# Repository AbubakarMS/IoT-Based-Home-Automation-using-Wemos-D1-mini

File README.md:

# IoT-Based-Home-Automation-using-Wemos-D1-mini
This project utilizes the D1 Mini and Blynk IoT platforms to monitor and control appliances. Users can switch appliances on and off through a mobile phone, providing a convenient and efficient home automation solution.

Note: A Kicad project files.

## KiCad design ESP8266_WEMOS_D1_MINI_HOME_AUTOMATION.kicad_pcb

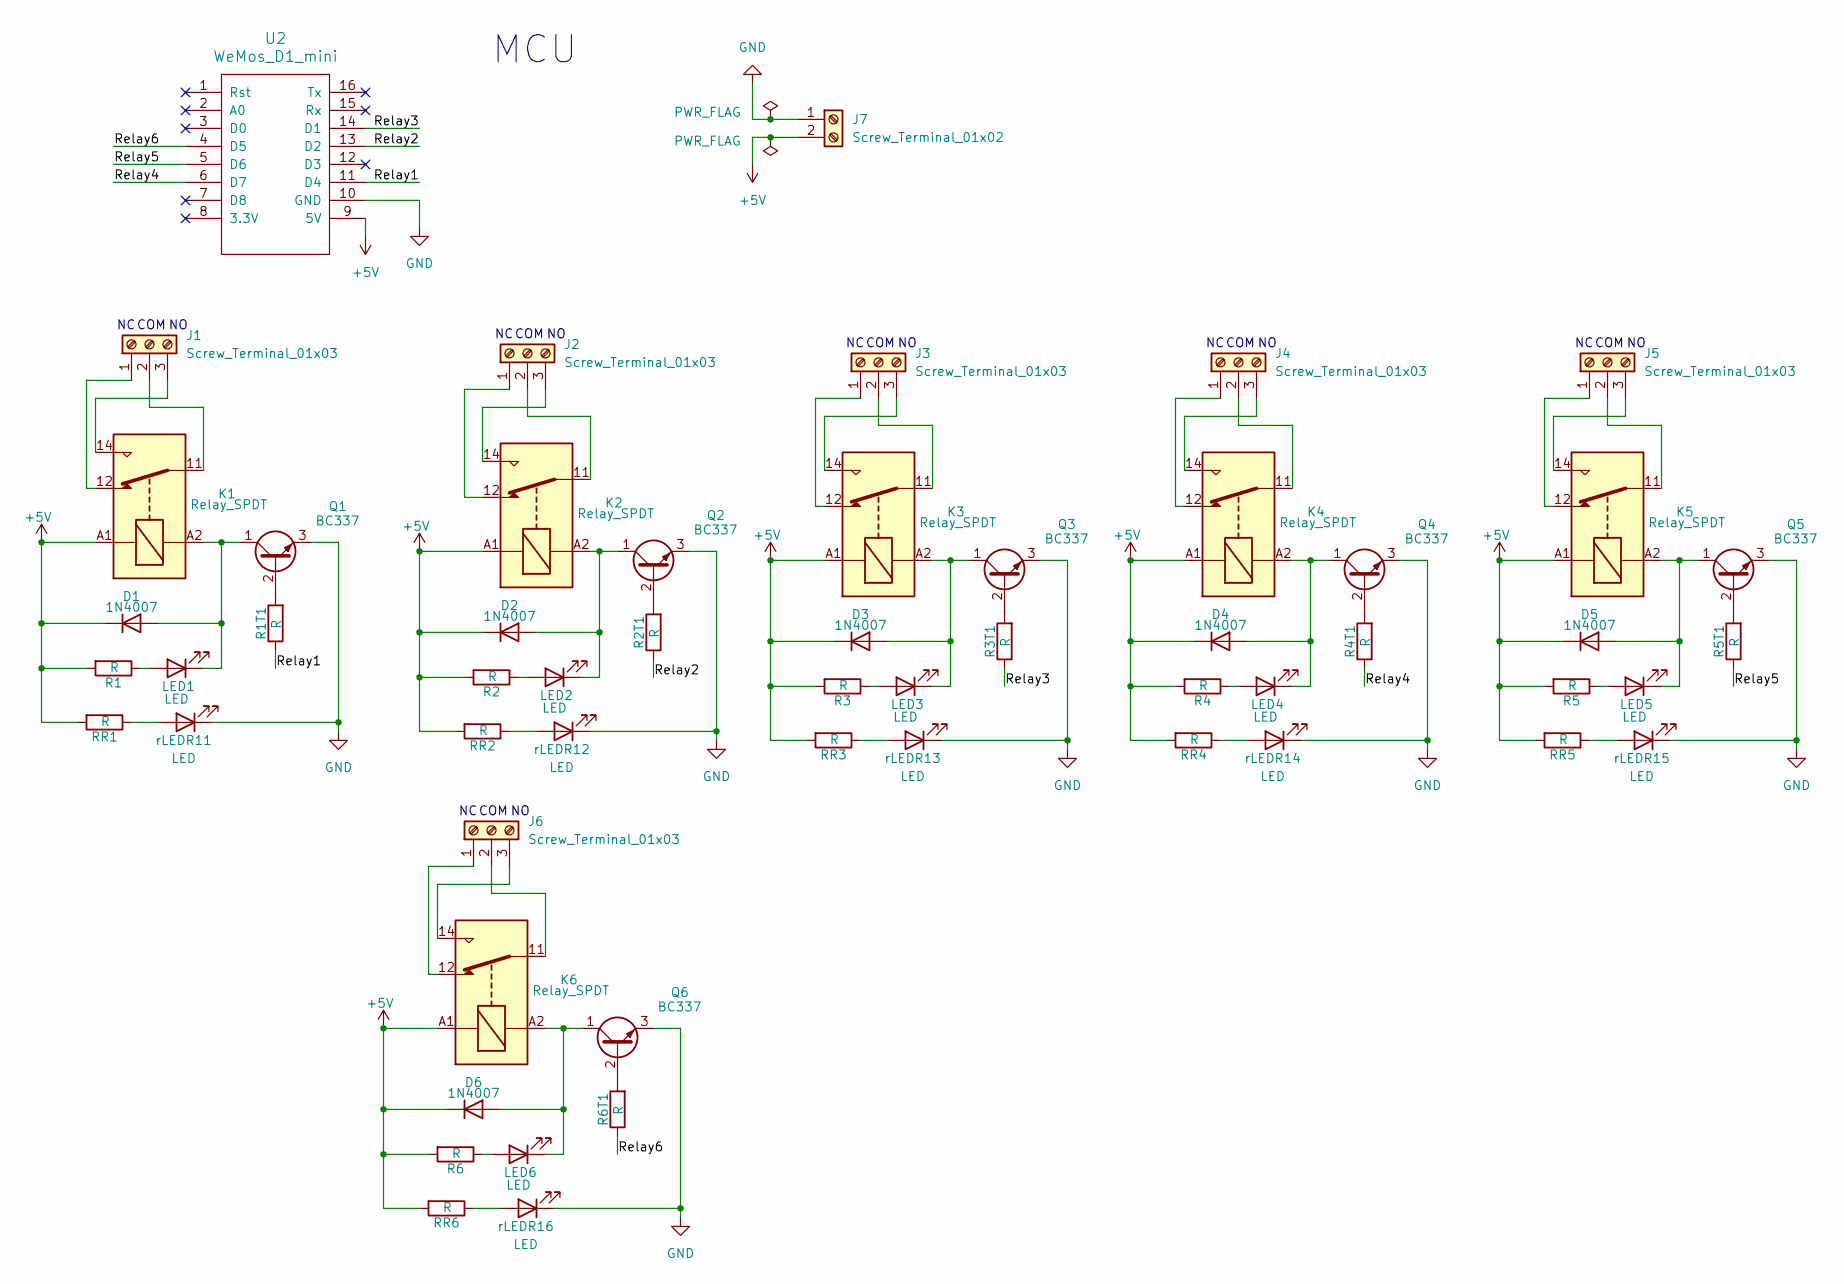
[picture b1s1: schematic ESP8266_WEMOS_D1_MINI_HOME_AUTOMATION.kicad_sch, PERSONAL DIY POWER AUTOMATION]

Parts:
D1, D2, D3, D4, D5, D6: 1N4007; D_DO-41_SOD81_P10.16mm_Horizontal
J1, J2, J3, J4, J5, J6: Screw_Terminal_01x03; TerminalBlock_MetzConnect_Type073_RT02603HBLU_1x03_P5.08mm_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
J7: Screw_Terminal_01x02; TerminalBlock_MetzConnect_Type073_RT02602HBLU_1x02_P5.08mm_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
K1, K2, K3, K4, K5, K6: Relay_SPDT; Relay_SPDT_Finder_36.11
LED1, LED2, LED3, LED4, LED5, LED6: LED; LED_D3.0mm_Clear
Q1, Q2, Q3, Q4, Q5, Q6: BC337; TO-92L_Inline
R1, R1T1, R2, R2T1, R3, R3T1, R4, R4T1, R5, R5T1, R6, R6T1: R; R_Axial_DIN0204_L3.6mm_D1.6mm_P5.08mm_Horizontal
RR1, RR2, RR3, RR4, RR5, RR6: R; R_Axial_DIN0204_L3.6mm_D1.6mm_P5.08mm_Horizontal
U2: WeMos_D1_mini; WEMOS_D1_mini_light
rLEDR11, rLEDR12, rLEDR13, rLEDR14, rLEDR15, rLEDR16: LED; LED_D3.0mm_Clear

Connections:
+5V: D1.1 (K), D2.1 (K), D3.1 (K), D4.1 (K), D5.1 (K), D6.1 (K), J7.2, K1.A1, K2.A1, K3.A1, K4.A1, K5.A1, K6.A1, R1.2, R2.2, R3.2, R4.2, R5.2, R6.2, RR1.2, RR2.2, RR3.2, RR4.2, RR5.2, RR6.2, U2.9 (5V)
/Relay1: R1T1.1, U2.11 (D4)
/Relay2: R2T1.1, U2.13 (D2)
/Relay3: R3T1.1, U2.14 (D1)
/Relay4: R4T1.1, U2.6 (D7)
/Relay5: R5T1.1, U2.5 (D6)
/Relay6: R6T1.1, U2.4 (D5)
GND: J7.1, Q1.3 (E), Q2.3 (E), Q3.3 (E), Q4.3 (E), Q5.3 (E), Q6.3 (E), U2.10 (GND), rLEDR11.1 (K), rLEDR12.1 (K), rLEDR13.1 (K), rLEDR14.1 (K), rLEDR15.1 (K), rLEDR16.1 (K)
unnamed: D1.2 (A), K1.A2, LED1.1 (K), Q1.1 (C)
unnamed: D2.2 (A), K2.A2, LED2.1 (K), Q2.1 (C)
unnamed: D3.2 (A), K3.A2, LED3.1 (K), Q3.1 (C)
unnamed: D4.2 (A), K4.A2, LED4.1 (K), Q4.1 (C)
unnamed: D5.2 (A), K5.A2, LED5.1 (K), Q5.1 (C)
unnamed: D6.2 (A), K6.A2, LED6.1 (K), Q6.1 (C)
unnamed: J1.1, K1.12
unnamed: J1.2, K1.11
unnamed: J1.3, K1.14
unnamed: J2.1, K2.12
unnamed: J2.2, K2.11
unnamed: J2.3, K2.14
unnamed: J3.1, K3.12
unnamed: J3.2, K3.11
unnamed: J3.3, K3.14
unnamed: J4.1, K4.12
unnamed: J4.2, K4.11
unnamed: J4.3, K4.14
unnamed: J5.1, K5.12
unnamed: J5.2, K5.11
unnamed: J5.3, K5.14
unnamed: J6.1, K6.12
unnamed: J6.2, K6.11
unnamed: J6.3, K6.14
unnamed: LED1.2 (A), R1.1
unnamed: LED2.2 (A), R2.1
unnamed: LED3.2 (A), R3.1
unnamed: LED4.2 (A), R4.1
unnamed: LED5.2 (A), R5.1
unnamed: LED6.2 (A), R6.1
unnamed: Q1.2 (B), R1T1.2
unnamed: Q2.2 (B), R2T1.2
unnamed: Q3.2 (B), R3T1.2
unnamed: Q4.2 (B), R4T1.2
unnamed: Q5.2 (B), R5T1.2
unnamed: Q6.2 (B), R6T1.2
unnamed: RR1.1, rLEDR11.2 (A)
unnamed: RR2.1, rLEDR12.2 (A)
unnamed: RR3.1, rLEDR13.2 (A)
unnamed: RR4.1, rLEDR14.2 (A)
unnamed: RR5.1, rLEDR15.2 (A)
unnamed: RR6.1, rLEDR16.2 (A)

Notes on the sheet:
MCU
COM

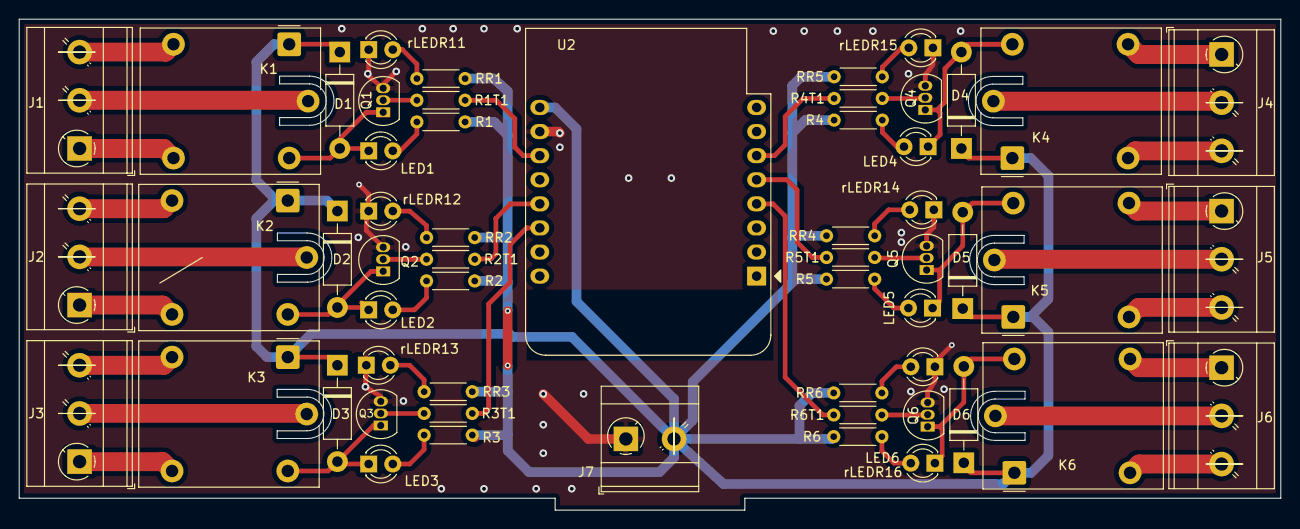
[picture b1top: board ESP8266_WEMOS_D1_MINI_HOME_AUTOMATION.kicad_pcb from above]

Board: 2 copper layers, 133.0 x 51.8 mm, 56 parts (0 on the bottom side), 50 nets.

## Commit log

2024-07-25 Create lib
2024-07-25 Main Files
2024-07-25 Update README.md
    Detailed pcb snapshot
